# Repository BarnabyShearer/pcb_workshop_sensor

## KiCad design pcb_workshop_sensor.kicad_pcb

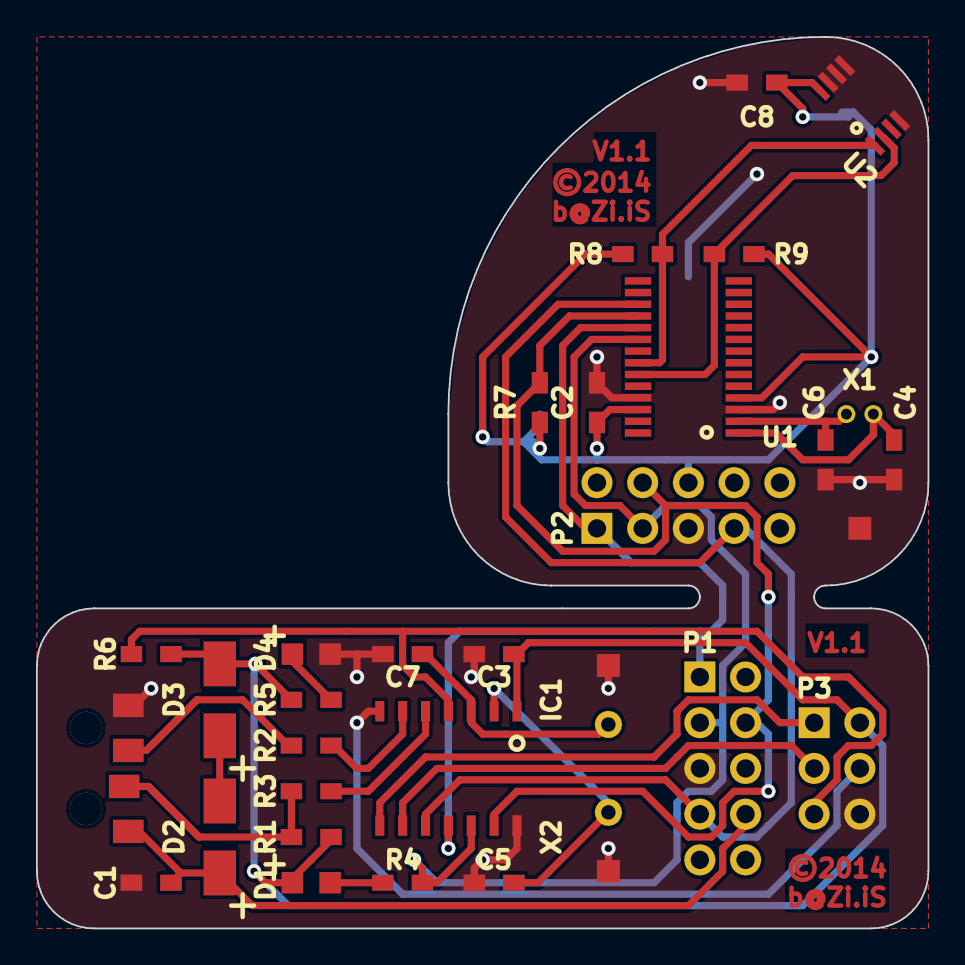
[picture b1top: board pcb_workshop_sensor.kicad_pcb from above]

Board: 2 copper layers, 49.5 x 49.5 mm, 31 parts (1 on the bottom side), 25 nets.

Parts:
BT1: BATTERY; BC-2001
C1: 4.7µF; 0603
C2, C3, C8: 0.1µF; 0603
C4, C6: 15pF; 0603
C5, C7: 27pF; 0603
D1: TX; LED-0805
D2, D3: DIODE; Diode-SMA_Standard
D4: POWER; LED-0805
IC1: ATTINY841-SSU; SOIC-14_N
J1: USB; USB_A_MC32604
P1, P2: BSL; Pin_Header_Straight_2x05
P3: ISP; Pin_Header_Straight_2x03
R1: 1k5; 0603
R2, R3, R4, R5: 68; 0603
R6, R7, R8, R9: 10k; 0603
U1: MSP430FR5738; TSSOP-28
U2: TMP275; MSOP-8
X1: 32768Hz; Crystal_Round_Horizontal_2mm
X2: 12MHz; Crystal_HC49-U_Vertical

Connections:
+5V: C1.1, D2.1, J1.1, P1.8
+BATT: BT1.1, C2.1, C8.1, P2.6, R7.2, R8.2, R9.2, U1.4, U1.26, U2.8
/AVR_DTR: IC1.13, P1.4, P2.4, R7.1, U1.18
/AVR_RST: IC1.4, P3.5, R6.1
/AVR_RTS: IC1.10, P1.7, P2.7, U1.17
/AVR_RX: IC1.11, P1.1, P2.1, U1.19
/AVR_TX: IC1.12, P1.3, P2.3, R4.1, U1.20
/D+: IC1.6, R2.1
/D-: IC1.5, R3.1
/MISO: IC1.8, P3.1
/MOSI: IC1.7, P3.4
/MSP_XTAL1: C4.2, U1.1, X1.1
/MSP_XTAL2: C6.2, U1.2, X1.2
/SCK: IC1.9, P3.3
/SCL: R8.1, U1.23, U2.2
/SDA: R9.1, U1.22, U2.1
/XTAL1: C5.2, IC1.2, X2.1
/XTAL2: C7.2, IC1.3, X2.2
GND: BT1.2, C1.2, C2.2, C3.2, C4.1, C5.1, C6.1, C7.1, C8.2, D4.2, IC1.14, J1.4, P1.5, P2.5, P3.6, U1.3, U1.25, U2.4, U2.5, U2.6, U2.7, X1.3, X2.3
unnamed: D1.2, R4.2
unnamed: D2.2, D3.1
unnamed: D4.1, R5.2
unnamed: J1.2, R1.1, R3.2
unnamed: J1.3, R2.2
VCC: C3.1, D1.1, D3.2, IC1.1, P3.2, R1.2, R5.1, R6.2

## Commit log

2014-10-27 v0.1
2014-10-31 v1.0
2014-11-30 repin for better layout

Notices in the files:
pcb_workshop_sensor.kicad_pcb:
©2014
